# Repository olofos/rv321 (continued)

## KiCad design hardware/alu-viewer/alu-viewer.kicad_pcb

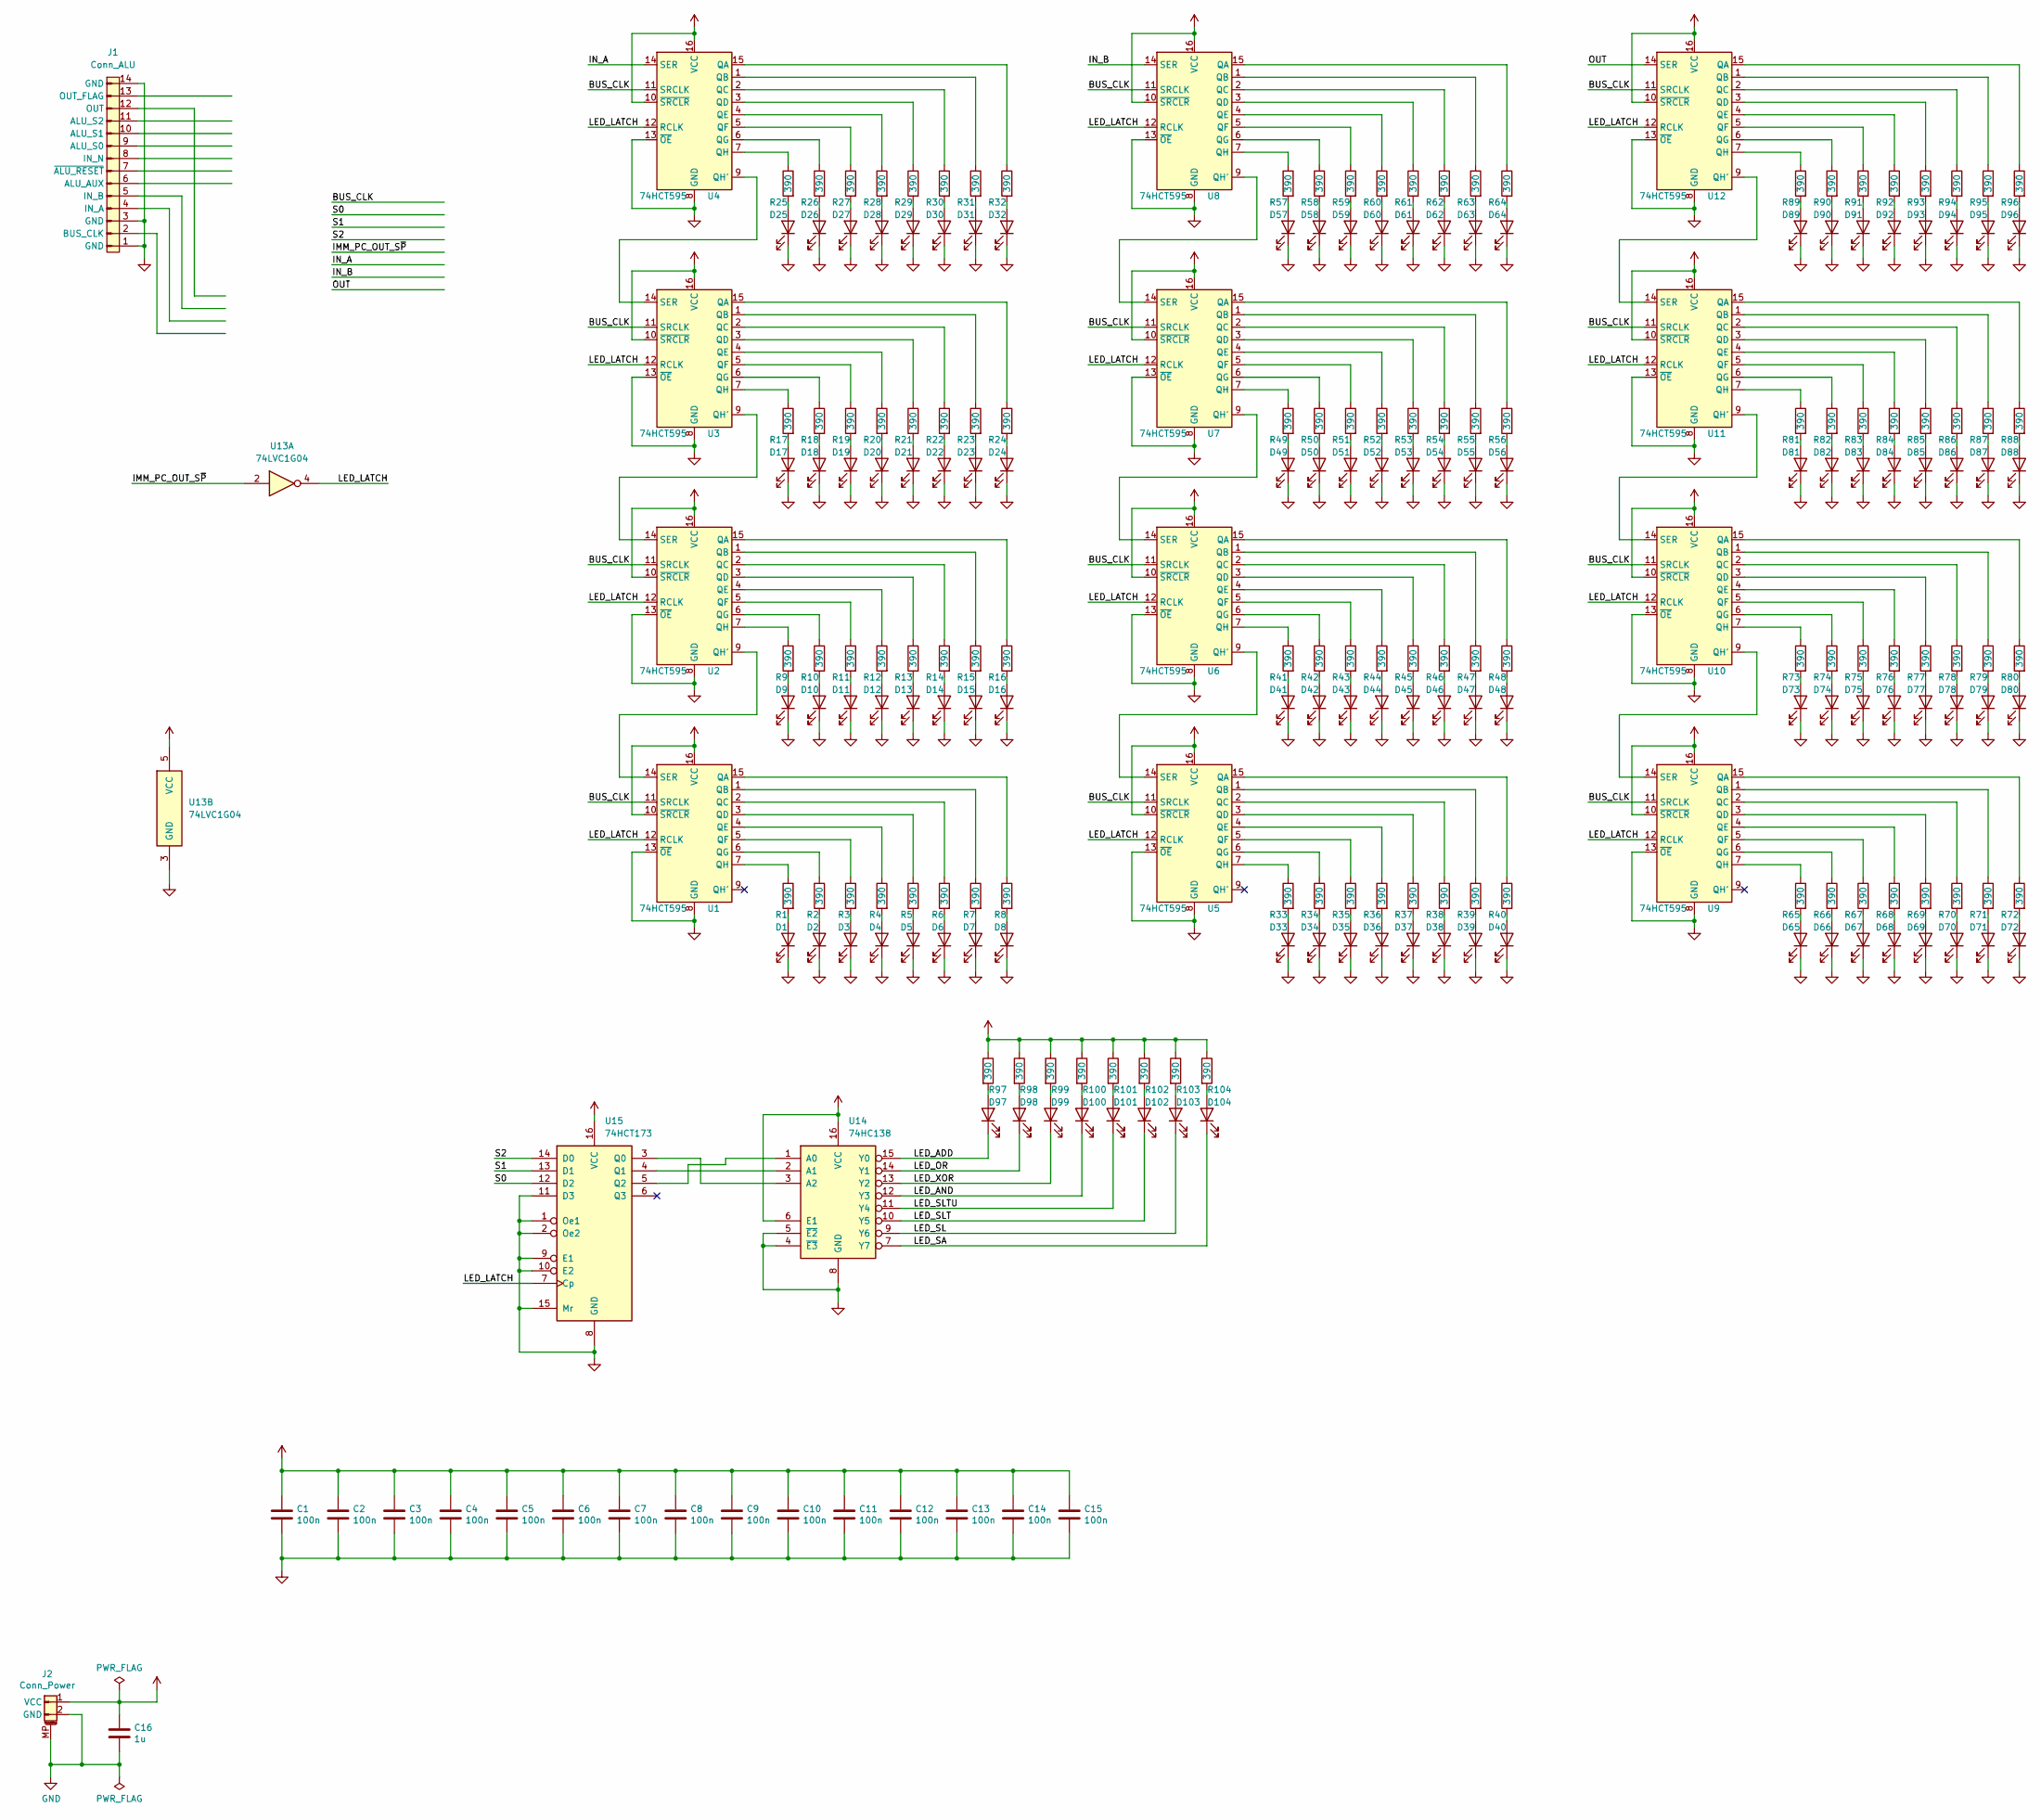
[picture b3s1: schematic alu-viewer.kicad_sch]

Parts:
C1, C2, C3, C4, C5, C6, C7, C8, C9, C10, C11, C12, C13, C14, C15: 100n; C_0805_2012Metric_Pad1.18x1.45mm_HandSolder
C16: 1u; C_0805_2012Metric_Pad1.18x1.45mm_HandSolder
D1, D2, D3, D4, D5, D6, D7, D8, D9, D10, D11, D12, D13, D14, D15, D16, D17, D18, D19, D20, D21, D22, D23, D24, D25, D26, D27, D28, D29, D30, D31, D32, D33, D34, D35, D36, D37, D38, D39, D40, D41, D42, D43, D44, D45, D46, D47, D48, D49, D50, D51, D52, D53, D54, D55, D56, D57, D58, D59, D60, D61, D62, D63, D64, D65, D66, D67, D68, D69, D70, D71, D72, D73, D74, D75, D76, D77, D78, D79, D80, D81, D82, D83, D84, D85, D86, D87, D88, D89, D90, D91, D92, D93, D94, D95, D96, D97, D98, D99, D100, D101, D102, D103, D104: LED; LED_0603_1608Metric
J1: Conn_ALU
J2: Conn_Power; JST_PH_S2B-PH-SM4-TB_1x02-1MP_P2.00mm_Horizontal
R1, R2, R3, R4, R5, R6, R7, R8, R9, R10, R11, R12, R13, R14, R15, R16, R17, R18, R19, R20, R21, R22, R23, R24, R25, R26, R27, R28, R29, R30, R31, R32, R33, R34, R35, R36, R37, R38, R39, R40, R41, R42, R43, R44, R45, R46, R47, R48, R49, R50, R51, R52, R53, R54, R55, R56, R57, R58, R59, R60, R61, R62, R63, R64, R65, R66, R67, R68, R69, R70, R71, R72, R73, R74, R75, R76, R77, R78, R79, R80, R81, R82, R83, R84, R85, R86, R87, R88, R89, R90, R91, R92, R93, R94, R95, R96, R97, R98, R99, R100, R101, R102, R103, R104: 390; R_0603_1608Metric
U1, U2, U3, U4, U5, U6, U7, U8, U9, U10, U11, U12: 74HCT595; SOIC-16_3.9x9.9mm_P1.27mm
U13: 74LVC1G04; SOT-23-5_HandSoldering
U14: 74HC138; SOIC-16_3.9x9.9mm_P1.27mm
U15: 74HCT173; SOIC-16_3.9x9.9mm_P1.27mm

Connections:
/BUS_CLK: U1.11 (SRCLK), U2.11 (SRCLK), U3.11 (SRCLK), U4.11 (SRCLK), U5.11 (SRCLK), U6.11 (SRCLK), U7.11 (SRCLK), U8.11 (SRCLK), U9.11 (SRCLK), U10.11 (SRCLK), U11.11 (SRCLK), U12.11 (SRCLK)
/IMM_PC_OUT_S~P: U13.2
/IN_A: U4.14 (SER)
/IN_B: U8.14 (SER)
/LED_ADD: D97.1 (K), U14.15 (Y0)
/LED_AND: D100.1 (K), U14.12 (Y3)
/LED_LATCH: U1.12 (RCLK), U2.12 (RCLK), U3.12 (RCLK), U4.12 (RCLK), U5.12 (RCLK), U6.12 (RCLK), U7.12 (RCLK), U8.12 (RCLK), U9.12 (RCLK), U10.12 (RCLK), U11.12 (RCLK), U12.12 (RCLK), U13.4, U15.7 (Cp)
/LED_OR: D98.1 (K), U14.14 (Y1)
/LED_SA: D104.1 (K), U14.7 (Y7)
/LED_SL: D103.1 (K), U14.9 (Y6)
/LED_SLT: D102.1 (K), U14.10 (Y5)
/LED_SLTU: D101.1 (K), U14.11 (Y4)
/LED_XOR: D99.1 (K), U14.13 (Y2)
/OUT: U12.14 (SER)
/S0: U15.12 (D2)
/S1: U15.13 (D1)
/S2: U15.14 (D0)
GND: C1.2, C2.2, C3.2, C4.2, C5.2, C6.2, C7.2, C8.2, C9.2, C10.2, C11.2, C12.2, C13.2, C14.2, C15.2, C16.2, D1.1 (K), D2.1 (K), D3.1 (K), D4.1 (K), D5.1 (K), D6.1 (K), D7.1 (K), D8.1 (K), D9.1 (K), D10.1 (K), D11.1 (K), D12.1 (K), D13.1 (K), D14.1 (K), D15.1 (K), D16.1 (K), D17.1 (K), D18.1 (K), D19.1 (K), D20.1 (K), D21.1 (K), D22.1 (K), D23.1 (K), D24.1 (K), D25.1 (K), D26.1 (K), D27.1 (K), D28.1 (K), D29.1 (K), D30.1 (K), D31.1 (K), D32.1 (K), D33.1 (K), D34.1 (K), D35.1 (K), D36.1 (K), D37.1 (K), D38.1 (K), D39.1 (K), D40.1 (K), D41.1 (K), D42.1 (K), D43.1 (K), D44.1 (K), D45.1 (K), D46.1 (K), D47.1 (K), D48.1 (K), D49.1 (K), D50.1 (K), D51.1 (K), D52.1 (K), D53.1 (K), D54.1 (K), D55.1 (K), D56.1 (K), D57.1 (K), D58.1 (K), D59.1 (K), D60.1 (K), D61.1 (K), D62.1 (K), D63.1 (K), D64.1 (K), D65.1 (K), D66.1 (K), D67.1 (K), D68.1 (K), D69.1 (K), D70.1 (K), D71.1 (K), D72.1 (K), D73.1 (K), D74.1 (K), D75.1 (K), D76.1 (K), D77.1 (K), D78.1 (K), D79.1 (K), D80.1 (K), D81.1 (K), D82.1 (K), D83.1 (K), D84.1 (K), D85.1 (K), D86.1 (K), D87.1 (K), D88.1 (K), D89.1 (K), D90.1 (K), D91.1 (K), D92.1 (K), D93.1 (K), D94.1 (K), D95.1 (K), D96.1 (K), J1.1 (GND), J1.3 (GND), J1.14 (GND), J2.2 (GND), J2.MP, U1.8 (GND), U1.13 (~OE), U2.8 (GND), U2.13 (~OE), U3.8 (GND), U3.13 (~OE), U4.8 (GND), U4.13 (~OE), U5.8 (GND), U5.13 (~OE), U6.8 (GND), U6.13 (~OE), U7.8 (GND), U7.13 (~OE), U8.8 (GND), U8.13 (~OE), U9.8 (GND), U9.13 (~OE), U10.8 (GND), U10.13 (~OE), U11.8 (GND), U11.13 (~OE), U12.8 (GND), U12.13 (~OE), U13.3 (GND), U14.4 (~E3), U14.5 (~E2), U14.8 (GND), U15.1 (Oe1), U15.2 (Oe2), U15.8 (GND), U15.9 (E1), U15.10 (E2), U15.11 (D3), U15.15 (Mr)
unnamed: D1.2 (A), R1.2
unnamed: D2.2 (A), R2.2
unnamed: D3.2 (A), R3.2
unnamed: D4.2 (A), R4.2
unnamed: D5.2 (A), R5.2
unnamed: D6.2 (A), R6.2
unnamed: D7.2 (A), R7.2
unnamed: D8.2 (A), R8.2
unnamed: D9.2 (A), R9.2
unnamed: D10.2 (A), R10.2
unnamed: D11.2 (A), R11.2
unnamed: D12.2 (A), R12.2
unnamed: D13.2 (A), R13.2
unnamed: D14.2 (A), R14.2
unnamed: D15.2 (A), R15.2
unnamed: D16.2 (A), R16.2
unnamed: D17.2 (A), R17.2
unnamed: D18.2 (A), R18.2
unnamed: D19.2 (A), R19.2
unnamed: D20.2 (A), R20.2
unnamed: D21.2 (A), R21.2
unnamed: D22.2 (A), R22.2
unnamed: D23.2 (A), R23.2
unnamed: D25.2 (A), R25.2
unnamed: D26.2 (A), R26.2
unnamed: D27.2 (A), R27.2
unnamed: D28.2 (A), R28.2
unnamed: D29.2 (A), R29.2
unnamed: D30.2 (A), R30.2
unnamed: D31.2 (A), R31.2
unnamed: D33.2 (A), R33.2
unnamed: D34.2 (A), R34.2
unnamed: D35.2 (A), R35.2
unnamed: D36.2 (A), R36.2
unnamed: D37.2 (A), R37.2
unnamed: D38.2 (A), R38.2
unnamed: D39.2 (A), R39.2
unnamed: D40.2 (A), R40.2
unnamed: D41.2 (A), R41.2
unnamed: D42.2 (A), R42.2
unnamed: D43.2 (A), R43.2
unnamed: D44.2 (A), R44.2
unnamed: D45.2 (A), R45.2
unnamed: D46.2 (A), R46.2
unnamed: D47.2 (A), R47.2
unnamed: D49.2 (A), R49.2
unnamed: D50.2 (A), R50.2
unnamed: D51.2 (A), R51.2
unnamed: D52.2 (A), R52.2
unnamed: D53.2 (A), R53.2
unnamed: D54.2 (A), R54.2
unnamed: D55.2 (A), R55.2
unnamed: D56.2 (A), R56.2
unnamed: D57.2 (A), R57.2
unnamed: D58.2 (A), R58.2
unnamed: D59.2 (A), R59.2
unnamed: D60.2 (A), R60.2
unnamed: D61.2 (A), R61.2
unnamed: D62.2 (A), R62.2
unnamed: D63.2 (A), R63.2
unnamed: D64.2 (A), R64.2
unnamed: D65.2 (A), R65.2
unnamed: D66.2 (A), R66.2
unnamed: D67.2 (A), R67.2
unnamed: D68.2 (A), R68.2
unnamed: D69.2 (A), R69.2
unnamed: D70.2 (A), R70.2
unnamed: D71.2 (A), R71.2
unnamed: D73.2 (A), R73.2
unnamed: D74.2 (A), R74.2
unnamed: D75.2 (A), R75.2
unnamed: D76.2 (A), R76.2
unnamed: D77.2 (A), R77.2
unnamed: D78.2 (A), R78.2
unnamed: D79.2 (A), R79.2
unnamed: D80.2 (A), R80.2
unnamed: D81.2 (A), R81.2
unnamed: D82.2 (A), R82.2
unnamed: D83.2 (A), R83.2
unnamed: D84.2 (A), R84.2
unnamed: D85.2 (A), R85.2
unnamed: D86.2 (A), R86.2
unnamed: D87.2 (A), R87.2
unnamed: D88.2 (A), R88.2
unnamed: D89.2 (A), R89.2
unnamed: D90.2 (A), R90.2
unnamed: D91.2 (A), R91.2
unnamed: D92.2 (A), R92.2
unnamed: D93.2 (A), R93.2
unnamed: D94.2 (A), R94.2
unnamed: D95.2 (A), R95.2
unnamed: D96.2 (A), R96.2
unnamed: D97.2 (A), R97.2
unnamed: D98.2 (A), R98.2
unnamed: D99.2 (A), R99.2
unnamed: D100.2 (A), R100.2
unnamed: D101.2 (A), R101.2
unnamed: D102.2 (A), R102.2
unnamed: D103.2 (A), R103.2
unnamed: D104.2 (A), R104.2
unnamed: R9.1, U2.7 (QH)
unnamed: R10.1, U2.6 (QG)
unnamed: R11.1, U2.5 (QF)
unnamed: R12.1, U2.4 (QE)
unnamed: R13.1, U2.3 (QD)
unnamed: R14.1, U2.2 (QC)
unnamed: R15.1, U2.1 (QB)
unnamed: R16.1, U2.15 (QA)
unnamed: R17.1, U3.7 (QH)
unnamed: R18.1, U3.6 (QG)
unnamed: R19.1, U3.5 (QF)
unnamed: R20.1, U3.4 (QE)
unnamed: R21.1, U3.3 (QD)
unnamed: R22.1, U3.2 (QC)
unnamed: R23.1, U3.1 (QB)
unnamed: R24.1, U3.15 (QA)
unnamed: D24.2 (A), R24.2
unnamed: R25.1, U4.7 (QH)
unnamed: R26.1, U4.6 (QG)
unnamed: R27.1, U4.5 (QF)
unnamed: R28.1, U4.4 (QE)
unnamed: R29.1, U4.3 (QD)
unnamed: R30.1, U4.2 (QC)
unnamed: R31.1, U4.1 (QB)
unnamed: R32.1, U4.15 (QA)
unnamed: D32.2 (A), R32.2
unnamed: R33.1, U5.7 (QH)
unnamed: R34.1, U5.6 (QG)
unnamed: R35.1, U5.5 (QF)
unnamed: R36.1, U5.4 (QE)
unnamed: R37.1, U5.3 (QD)
unnamed: R38.1, U5.2 (QC)
unnamed: R39.1, U5.1 (QB)
unnamed: R40.1, U5.15 (QA)
unnamed: R41.1, U6.7 (QH)
unnamed: R42.1, U6.6 (QG)
unnamed: R43.1, U6.5 (QF)
unnamed: R44.1, U6.4 (QE)
unnamed: R45.1, U6.3 (QD)
unnamed: R46.1, U6.2 (QC)
unnamed: R47.1, U6.1 (QB)
unnamed: R48.1, U6.15 (QA)
unnamed: D48.2 (A), R48.2
unnamed: R49.1, U7.7 (QH)
unnamed: R50.1, U7.6 (QG)
unnamed: R51.1, U7.5 (QF)
unnamed: R52.1, U7.4 (QE)
unnamed: R53.1, U7.3 (QD)
unnamed: R54.1, U7.2 (QC)
unnamed: R55.1, U7.1 (QB)
unnamed: R56.1, U7.15 (QA)
unnamed: R57.1, U8.7 (QH)
unnamed: R58.1, U8.6 (QG)
unnamed: R59.1, U8.5 (QF)
unnamed: R60.1, U8.4 (QE)
unnamed: R61.1, U8.3 (QD)
unnamed: R62.1, U8.2 (QC)
unnamed: R63.1, U8.1 (QB)
unnamed: R64.1, U8.15 (QA)
unnamed: R65.1, U9.7 (QH)
unnamed: R66.1, U9.6 (QG)
unnamed: R67.1, U9.5 (QF)
unnamed: R68.1, U9.4 (QE)
unnamed: R69.1, U9.3 (QD)
unnamed: R70.1, U9.2 (QC)
unnamed: R71.1, U9.1 (QB)
unnamed: R72.1, U9.15 (QA)
unnamed: D72.2 (A), R72.2
unnamed: R73.1, U10.7 (QH)
unnamed: R74.1, U10.6 (QG)
unnamed: R75.1, U10.5 (QF)
unnamed: R76.1, U10.4 (QE)
unnamed: R77.1, U10.3 (QD)
unnamed: R78.1, U10.2 (QC)
unnamed: R79.1, U10.1 (QB)
unnamed: R80.1, U10.15 (QA)
unnamed: R81.1, U11.7 (QH)
unnamed: R82.1, U11.6 (QG)
unnamed: R83.1, U11.5 (QF)
unnamed: R84.1, U11.4 (QE)
unnamed: R85.1, U11.3 (QD)
unnamed: R86.1, U11.2 (QC)
unnamed: R87.1, U11.1 (QB)
unnamed: R88.1, U11.15 (QA)
unnamed: R89.1, U12.7 (QH)
unnamed: R90.1, U12.6 (QG)
unnamed: R91.1, U12.5 (QF)
unnamed: R92.1, U12.4 (QE)
unnamed: R93.1, U12.3 (QD)
unnamed: R94.1, U12.2 (QC)
unnamed: R95.1, U12.1 (QB)
unnamed: R96.1, U12.15 (QA)
unnamed: R7.1, U1.1 (QB)
unnamed: R6.1, U1.2 (QC)
unnamed: R5.1, U1.3 (QD)
unnamed: R4.1, U1.4 (QE)
unnamed: R3.1, U1.5 (QF)
unnamed: R2.1, U1.6 (QG)
unnamed: R1.1, U1.7 (QH)
unnamed: U1.14 (SER), U2.9 (QH')
unnamed: R8.1, U1.15 (QA)
unnamed: U2.14 (SER), U3.9 (QH')
unnamed: U3.14 (SER), U4.9 (QH')
unnamed: U5.14 (SER), U6.9 (QH')
unnamed: U6.14 (SER), U7.9 (QH')
unnamed: U7.14 (SER), U8.9 (QH')
unnamed: U9.14 (SER), U10.9 (QH')
unnamed: U10.14 (SER), U11.9 (QH')
unnamed: U11.14 (SER), U12.9 (QH')
unnamed: U14.1 (A0), U15.5 (Q2)
unnamed: U14.2 (A1), U15.4 (Q1)
unnamed: U14.3 (A2), U15.3 (Q0)
VCC: C1.1, C2.1, C3.1, C4.1, C5.1, C6.1, C7.1, C8.1, C9.1, C10.1, C11.1, C12.1, C13.1, C14.1, C15.1, C16.1, J2.1 (VCC), R97.1, R98.1, R99.1, R100.1, R101.1, R102.1, R103.1, R104.1, U1.10 (~SRCLR), U1.16 (VCC), U2.10 (~SRCLR), U2.16 (VCC), U3.10 (~SRCLR), U3.16 (VCC), U4.10 (~SRCLR), U4.16 (VCC), U5.10 (~SRCLR), U5.16 (VCC), U6.10 (~SRCLR), U6.16 (VCC), U7.10 (~SRCLR), U7.16 (VCC), U8.10 (~SRCLR), U8.16 (VCC), U9.10 (~SRCLR), U9.16 (VCC), U10.10 (~SRCLR), U10.16 (VCC), U11.10 (~SRCLR), U11.16 (VCC), U12.10 (~SRCLR), U12.16 (VCC), U13.5 (VCC), U14.6 (E1), U14.16 (VCC), U15.16 (VCC)

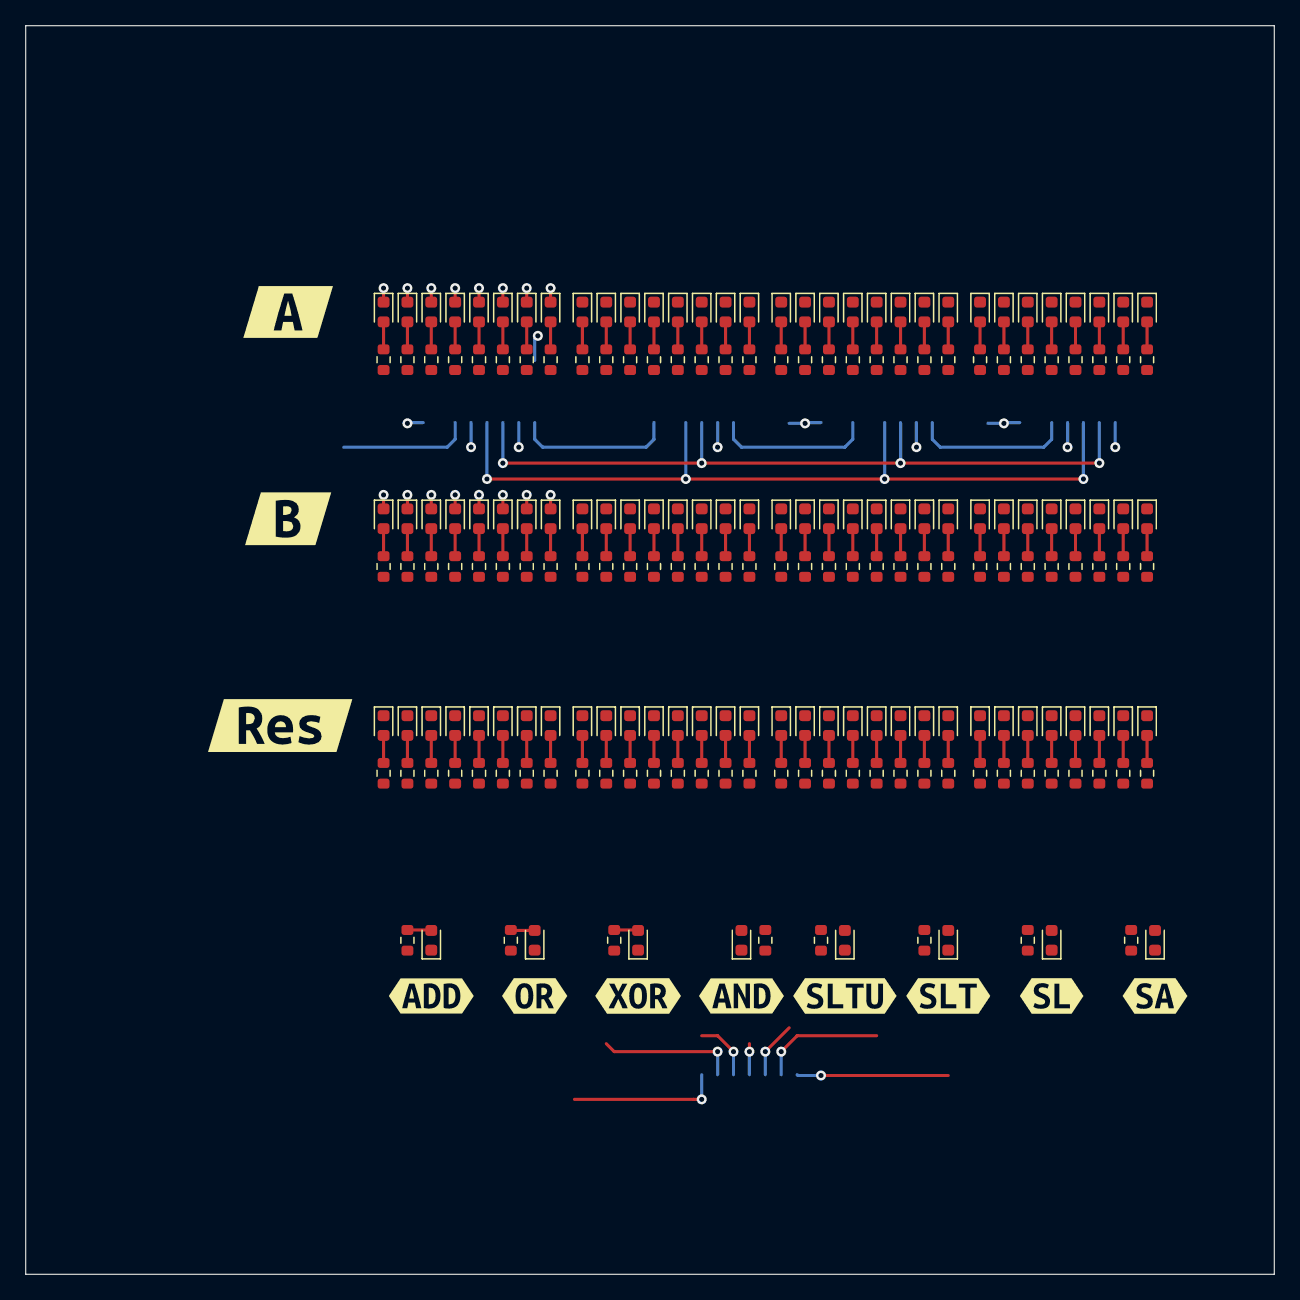
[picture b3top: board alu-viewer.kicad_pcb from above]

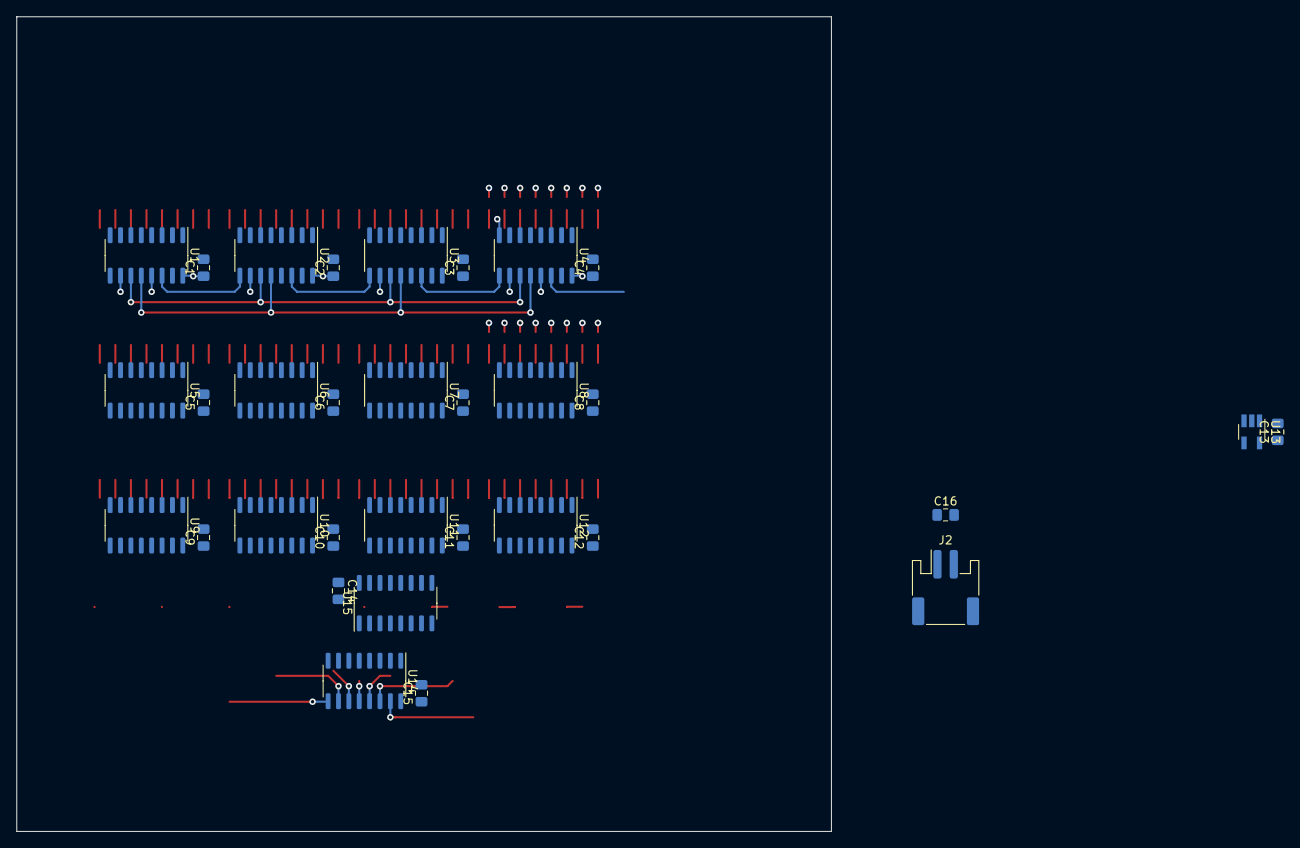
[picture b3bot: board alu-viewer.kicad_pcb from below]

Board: 4 copper layers, 99.7 x 99.7 mm, 251 parts (32 on the bottom side), 224 nets.

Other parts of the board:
kibuzzard-631087D5: G***; kibuzzard-631087D5
kibuzzard-631087E9: G***; kibuzzard-631087E9
kibuzzard-631088E6: G***; kibuzzard-631088E6
kibuzzard-631088FC: G***; kibuzzard-631088FC
kibuzzard-631089CA: G***; kibuzzard-631089CA
kibuzzard-6310893A: G***; kibuzzard-6310893A
kibuzzard-6310894E: G***; kibuzzard-6310894E
kibuzzard-6310895A: G***; kibuzzard-6310895A
kibuzzard-63108921: G***; kibuzzard-63108921
kibuzzard-63108965: G***; kibuzzard-63108965
kibuzzard-63108972: G***; kibuzzard-63108972

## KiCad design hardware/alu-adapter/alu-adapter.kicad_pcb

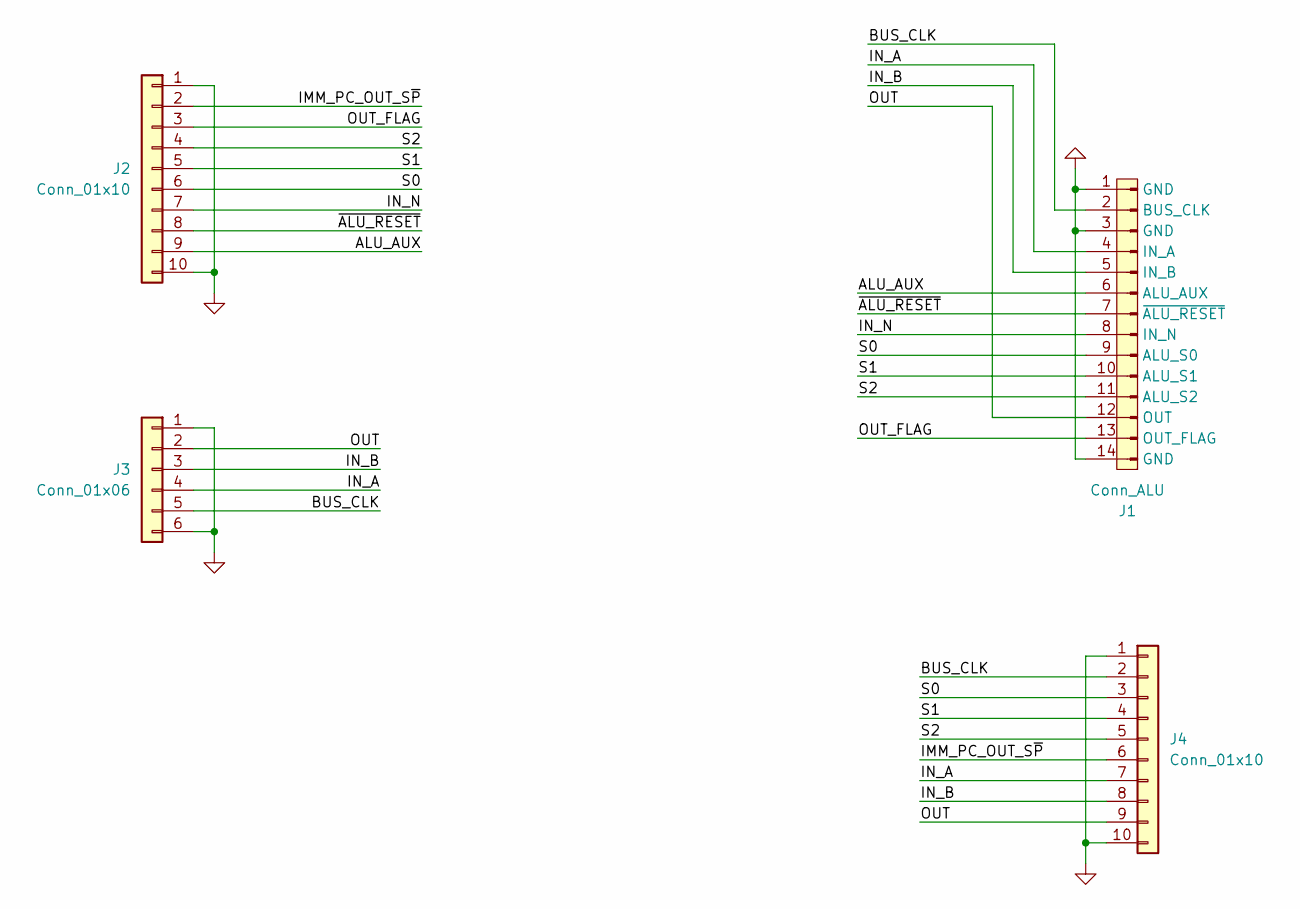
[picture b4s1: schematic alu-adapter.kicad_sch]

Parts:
J1: Conn_ALU; IDC-Header_2x07_P2.54mm_Vertical
J2, J4: Conn_01x10; IDC-Header_2x05_P2.54mm_Vertical
J3: Conn_01x06; IDC-Header_2x03_P2.54mm_Vertical

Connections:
/ALU_AUX: J1.6 (ALU_AUX), J2.9
/BUS_CLK: J1.2 (BUS_CLK), J3.5, J4.2
/IMM_PC_OUT_S~P: J2.2, J4.6
/IN_A: J1.4 (IN_A), J3.4, J4.7
/IN_B: J1.5 (IN_B), J3.3, J4.8
/IN_N: J1.8 (IN_N), J2.7
/OUT: J1.12 (OUT), J3.2, J4.9
/OUT_FLAG: J1.13 (OUT_FLAG), J2.3
/S0: J1.9 (ALU_S0), J2.6, J4.3
/S1: J1.10 (ALU_S1), J2.5, J4.4
/S2: J1.11 (ALU_S2), J2.4, J4.5
/~ALU_RESET: J1.7 (~ALU_RESET), J2.8
GND: J1.1 (GND), J1.3 (GND), J1.14 (GND), J2.1, J2.10, J3.1, J3.6, J4.1, J4.10

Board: 2 copper layers, 4 parts (0 on the bottom side), 13 nets, no tracks yet.

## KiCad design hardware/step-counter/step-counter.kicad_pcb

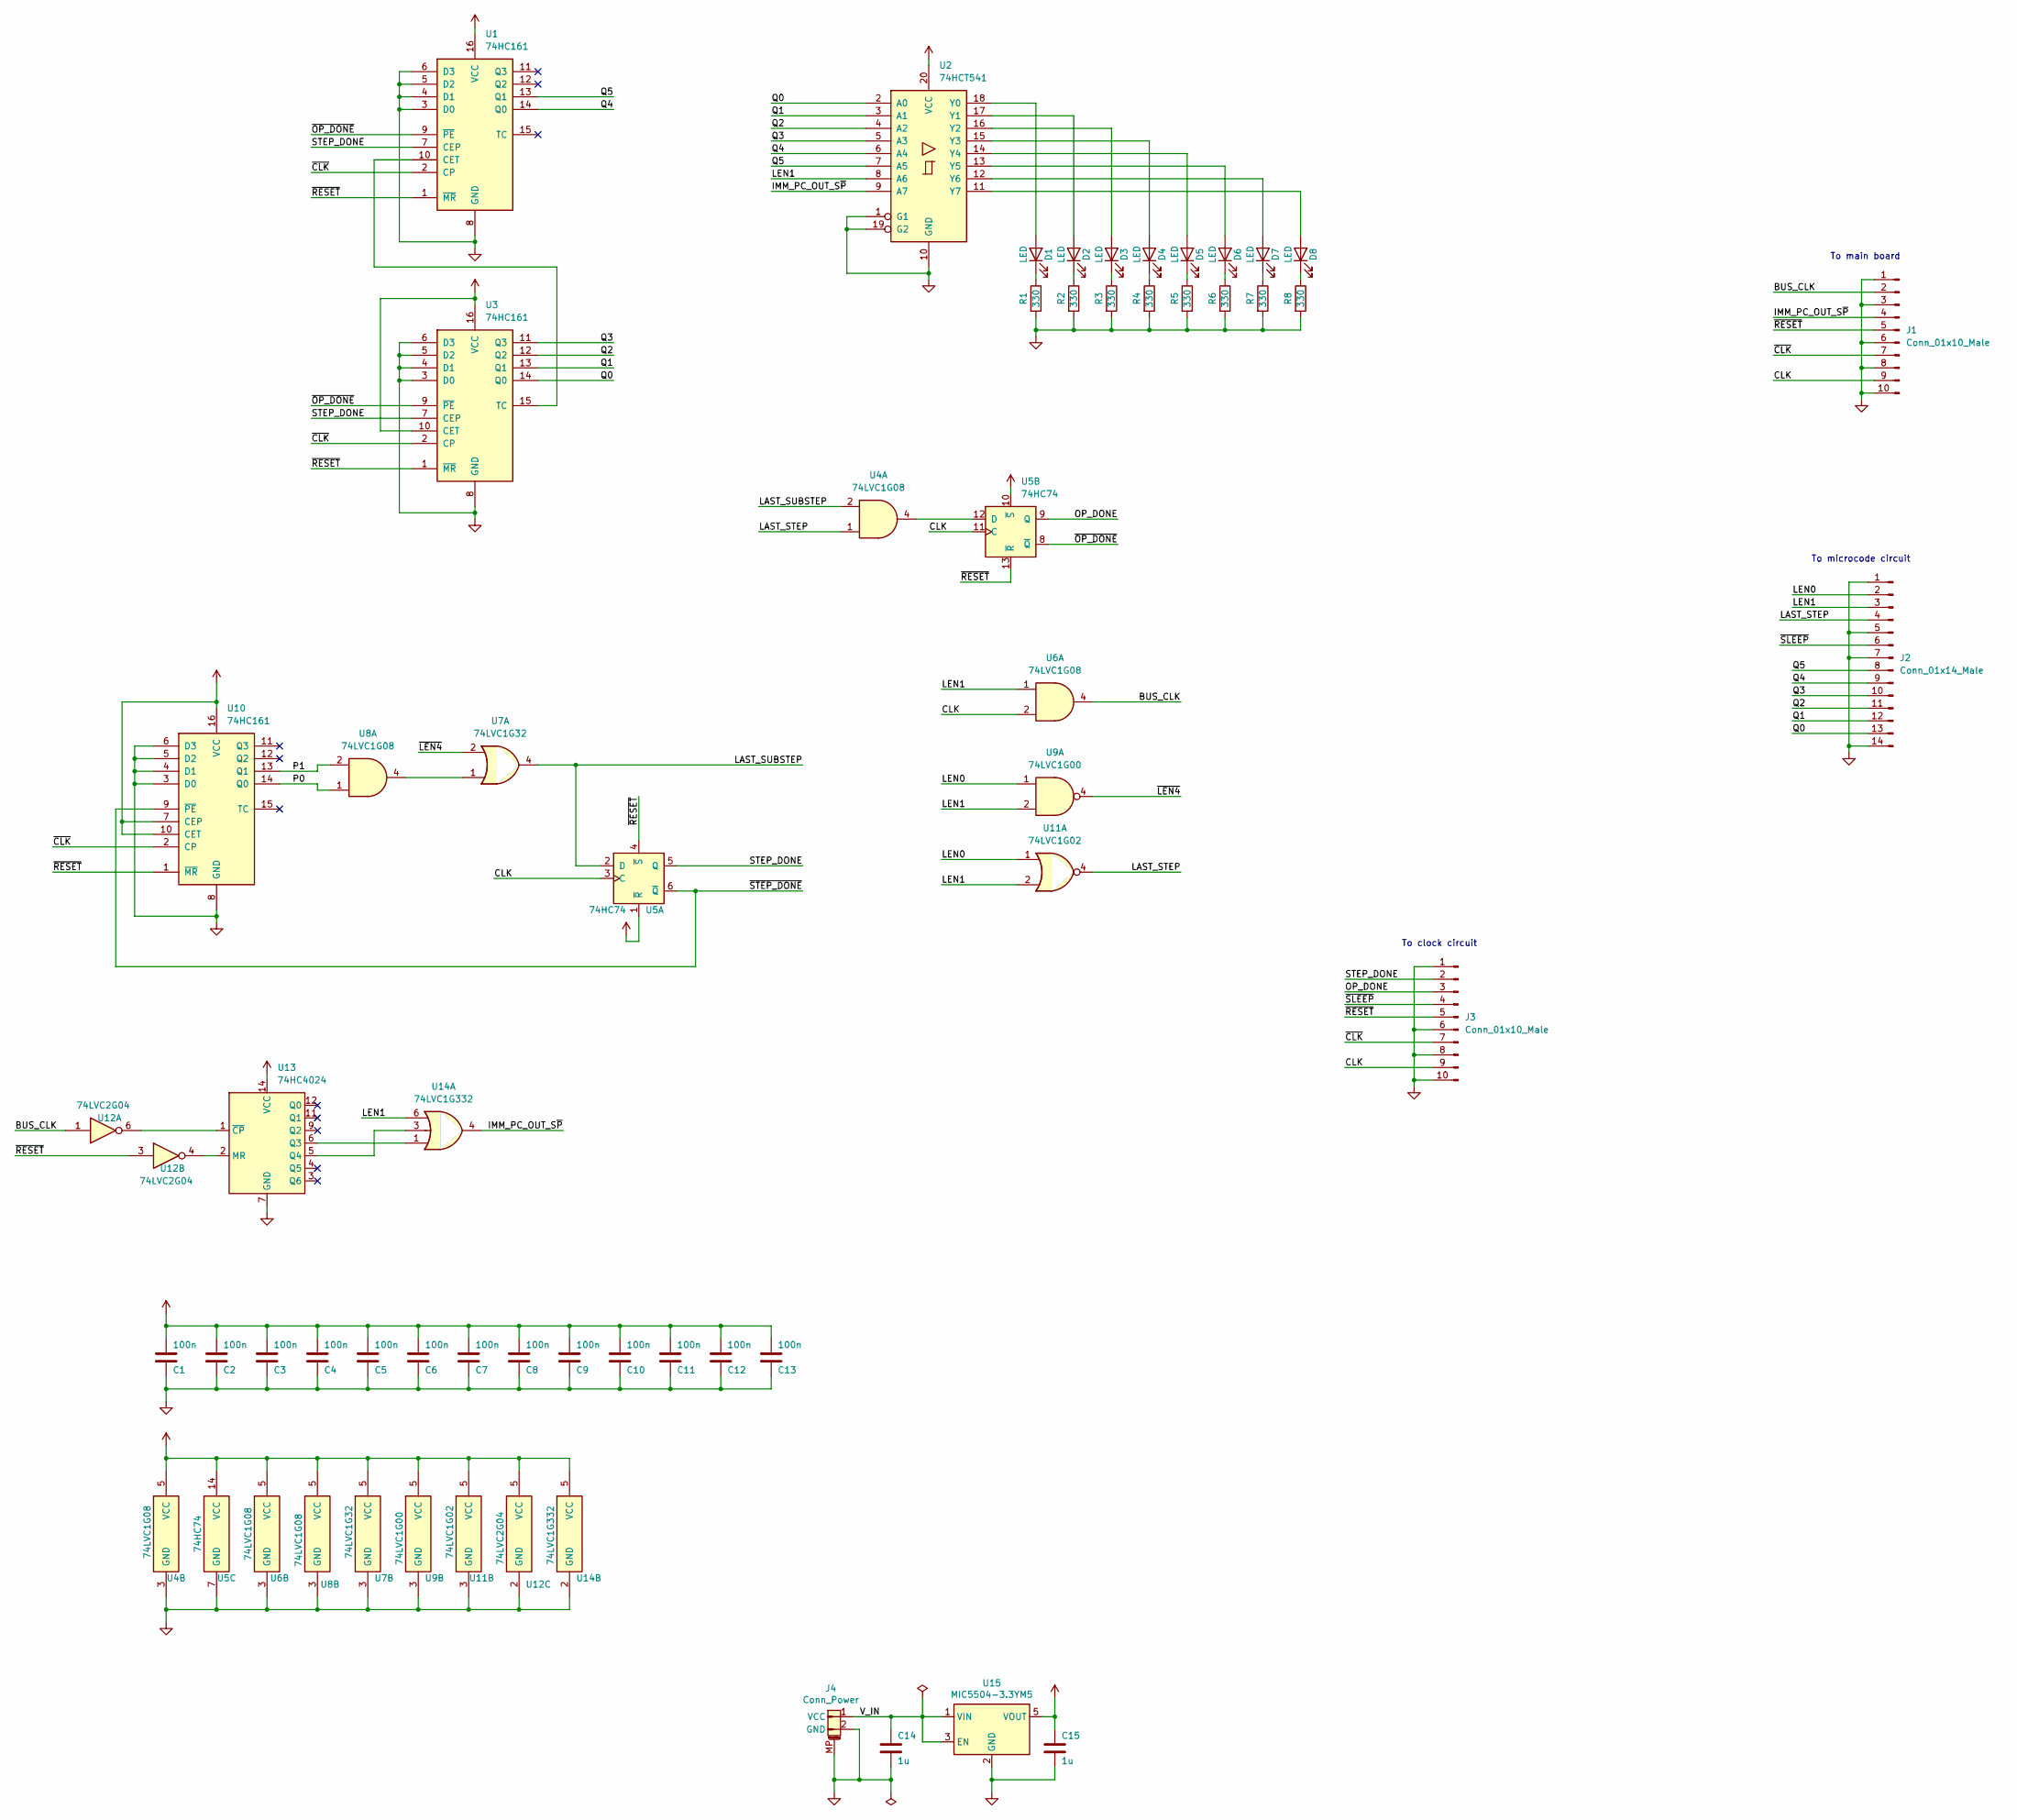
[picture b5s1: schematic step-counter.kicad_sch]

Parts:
C1, C2, C3, C4, C5, C6, C7, C8, C9, C10, C11, C12, C13: 100n; C_0805_2012Metric_Pad1.18x1.45mm_HandSolder
C14, C15: 1u; C_0805_2012Metric_Pad1.18x1.45mm_HandSolder
D1, D2, D3, D4, D5, D6, D7, D8: LED; LED_0805_2012Metric_Pad1.15x1.40mm_HandSolder
J1, J3: Conn_01x10_Male; IDC-Header_2x05_P2.54mm_Vertical
J2: Conn_01x14_Male; IDC-Header_2x07_P2.54mm_Vertical
J4: Conn_Power; JST_PH_S2B-PH-SM4-TB_1x02-1MP_P2.00mm_Horizontal
R1, R2, R3, R4, R5, R6, R7, R8: 330; R_0805_2012Metric_Pad1.20x1.40mm_HandSolder
U1, U3, U10: 74HC161; SOIC-16_3.9x9.9mm_P1.27mm
U2: 74HCT541; TSSOP-20_4.4x6.5mm_P0.65mm
U4, U6, U8: 74LVC1G08; SOT-23-5_HandSoldering
U5: 74HC74; SOIC-14_3.9x8.7mm_P1.27mm
U7: 74LVC1G32; SOT-23-5_HandSoldering
U9: 74LVC1G00; SOT-23-5_HandSoldering
U11: 74LVC1G02; SOT-23-5_HandSoldering
U12: 74LVC2G04; SOT-23-6_Handsoldering
U13: 74HC4024; SOIC-14_3.9x8.7mm_P1.27mm
U14: 74LVC1G332; SOT-23-6_Handsoldering
U15: MIC5504-3.3YM5; SOT-23-5

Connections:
/BUS_CLK: J1.2, U6.4, U12.1
/CLK: J1.9, J3.9, U5.3 (C), U5.11 (C), U6.2
/IMM_PC_OUT_S~P: J1.4, U2.9 (A7), U14.4
/LAST_STEP: J2.4, U4.1, U11.4
/LAST_SUBSTEP: U4.2, U5.2 (D), U7.4
/LEN0: J2.2, U9.1, U11.1
/LEN1: J2.3, U2.8 (A6), U6.1, U9.2, U11.2, U14.6
/OP_DONE: J3.3, U5.9 (Q)
/P0: U8.1, U10.14 (Q0)
/P1: U8.2, U10.13 (Q1)
/Q0: J2.13, U2.2 (A0), U3.14 (Q0)
/Q1: J2.12, U2.3 (A1), U3.13 (Q1)
/Q2: J2.11, U2.4 (A2), U3.12 (Q2)
/Q3: J2.10, U2.5 (A3), U3.11 (Q3)
/Q4: J2.9, U1.14 (Q0), U2.6 (A4)
/Q5: J2.8, U1.13 (Q1), U2.7 (A5)
/STEP_DONE: J3.2, U1.7 (CEP), U3.7 (CEP), U5.5 (Q)
/V_IN: C14.1, J4.1 (VCC), U15.1 (VIN), U15.3 (EN)
/~CLK: J1.7, J3.7, U1.2 (CP), U3.2 (CP), U10.2 (CP)
/~LEN4: U7.2, U9.4
/~OP_DONE: U1.9 (~PE), U3.9 (~PE), U5.8 (~Q)
/~RESET: J1.5, J3.5, U1.1 (~MR), U3.1 (~MR), U5.4 (~S), U5.13 (~R), U10.1 (~MR), U12.3
/~SLEEP: J2.6, J3.4
/~STEP_DONE: U5.6 (~Q), U10.9 (~PE)
GND: C1.2, C2.2, C3.2, C4.2, C5.2, C6.2, C7.2, C8.2, C9.2, C10.2, C11.2, C12.2, C13.2, C14.2, C15.2, J1.1, J1.3, J1.6, J1.8, J1.10, J2.1, J2.5, J2.7, J2.14, J3.1, J3.6, J3.8, J3.10, J4.2 (GND), J4.MP, R1.2, R2.2, R3.2, R4.2, R5.2, R6.2, R7.2, R8.2, U1.3 (D0), U1.4 (D1), U1.5 (D2), U1.6 (D3), U1.8 (GND), U2.1 (G1), U2.10 (GND), U2.19 (G2), U3.3 (D0), U3.4 (D1), U3.5 (D2), U3.6 (D3), U3.8 (GND), U4.3 (GND), U5.7 (GND), U6.3 (GND), U7.3 (GND), U8.3 (GND), U9.3 (GND), U10.3 (D0), U10.4 (D1), U10.5 (D2), U10.6 (D3), U10.8 (GND), U11.3 (GND), U12.2 (GND), U13.7 (GND), U14.2 (GND), U15.2 (GND)
unnamed: D1.1 (K), R1.1
unnamed: D1.2 (A), U2.18 (Y0)
unnamed: D2.1 (K), R2.1
unnamed: D2.2 (A), U2.17 (Y1)
unnamed: D3.1 (K), R3.1
unnamed: D3.2 (A), U2.16 (Y2)
unnamed: D4.1 (K), R4.1
unnamed: D4.2 (A), U2.15 (Y3)
unnamed: D5.1 (K), R5.1
unnamed: D5.2 (A), U2.14 (Y4)
unnamed: D6.1 (K), R6.1
unnamed: D6.2 (A), U2.13 (Y5)
unnamed: D7.1 (K), R7.1
unnamed: D7.2 (A), U2.12 (Y6)
unnamed: D8.1 (K), R8.1
unnamed: D8.2 (A), U2.11 (Y7)
unnamed: U1.10 (CET), U3.15 (TC)
unnamed: U4.4, U5.12 (D)
unnamed: U7.1, U8.4
unnamed: U12.4, U13.2 (MR)
unnamed: U12.6, U13.1 (~CP)
unnamed: U13.5 (Q4), U14.3
unnamed: U13.6 (Q3), U14.1
VCC: C1.1, C2.1, C3.1, C4.1, C5.1, C6.1, C7.1, C8.1, C9.1, C10.1, C11.1, C12.1, C13.1, C15.1, U1.16 (VCC), U2.20 (VCC), U3.10 (CET), U3.16 (VCC), U4.5 (VCC), U5.1 (~R), U5.10 (~S), U5.14 (VCC), U6.5 (VCC), U7.5 (VCC), U8.5 (VCC), U9.5 (VCC), U10.7 (CEP), U10.10 (CET), U10.16 (VCC), U11.5 (VCC), U12.5 (VCC), U13.14 (VCC), U14.5 (VCC), U15.5 (VOUT)

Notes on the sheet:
To main board
To microcode circuit
To clock circuit
